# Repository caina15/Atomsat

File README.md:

# Atomsat
Atomsat is a 9-member project, the aim of the project is to develop and launch a low-cost cubesat 1U (nano satellite in cube format 10 by 10 by 10 cm) for technology demonstration and open doors for scientific experiments in schools around the world . The launch estimate is for the beginning of 2024 and is expected to be in operation for 1 year (caused by orbital decay).
(The project is still under development, codes and PCBs are not ready)

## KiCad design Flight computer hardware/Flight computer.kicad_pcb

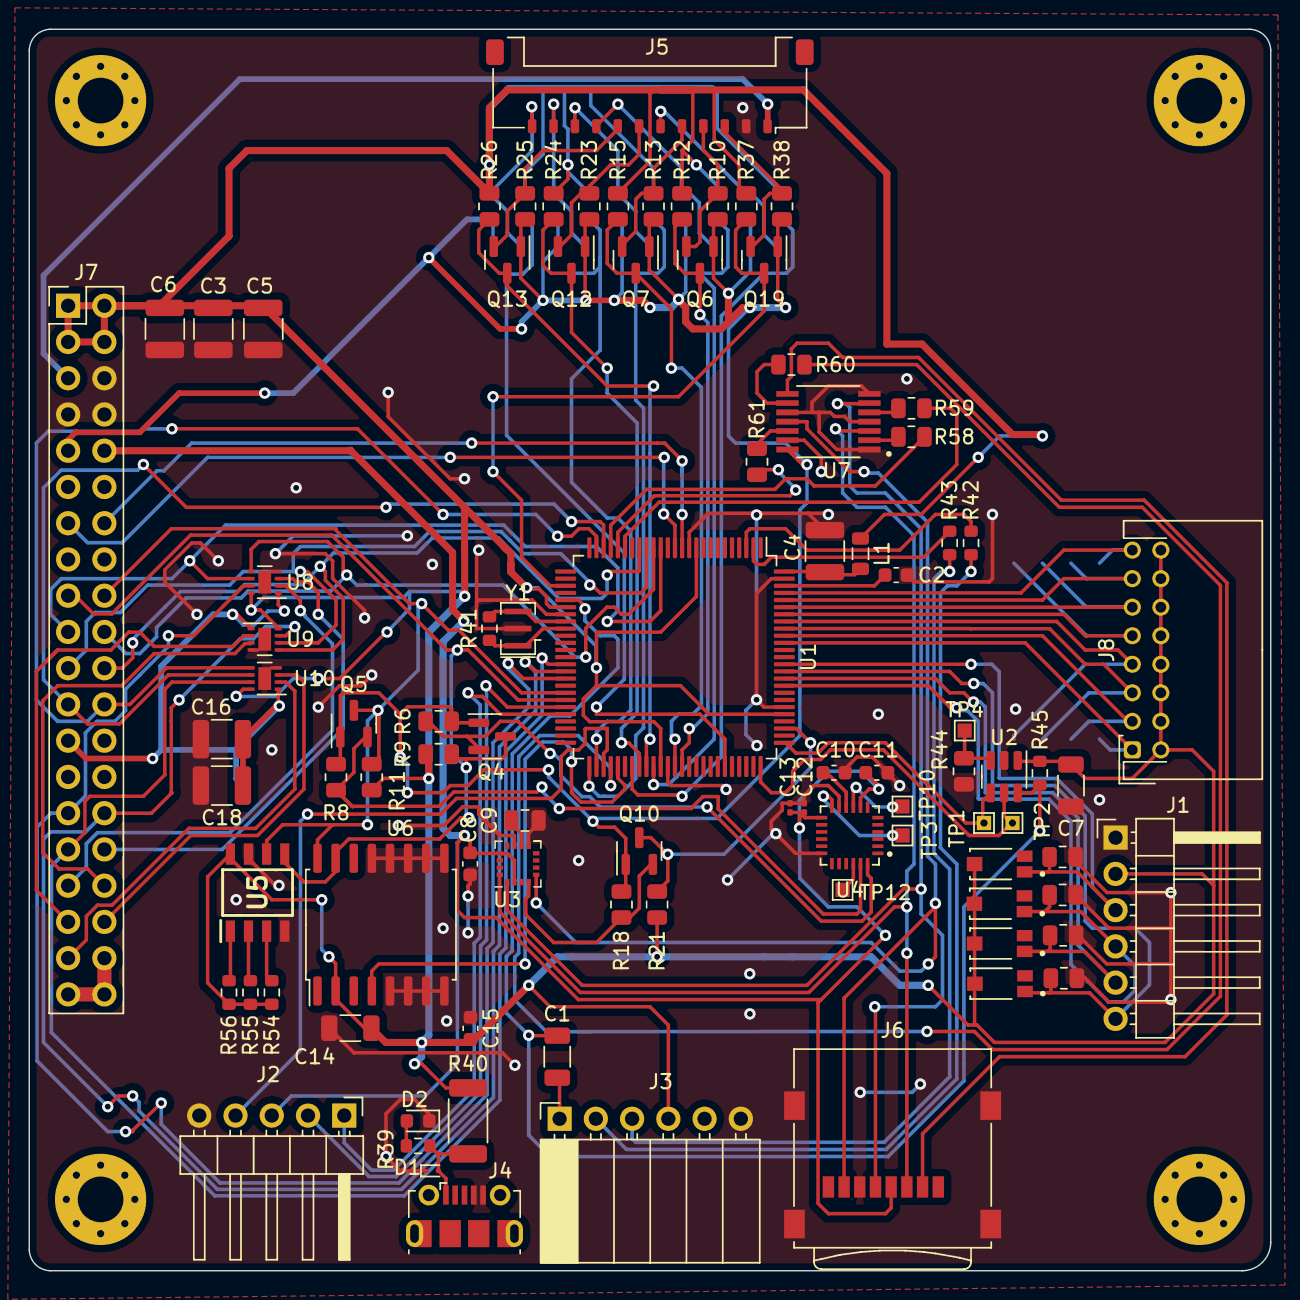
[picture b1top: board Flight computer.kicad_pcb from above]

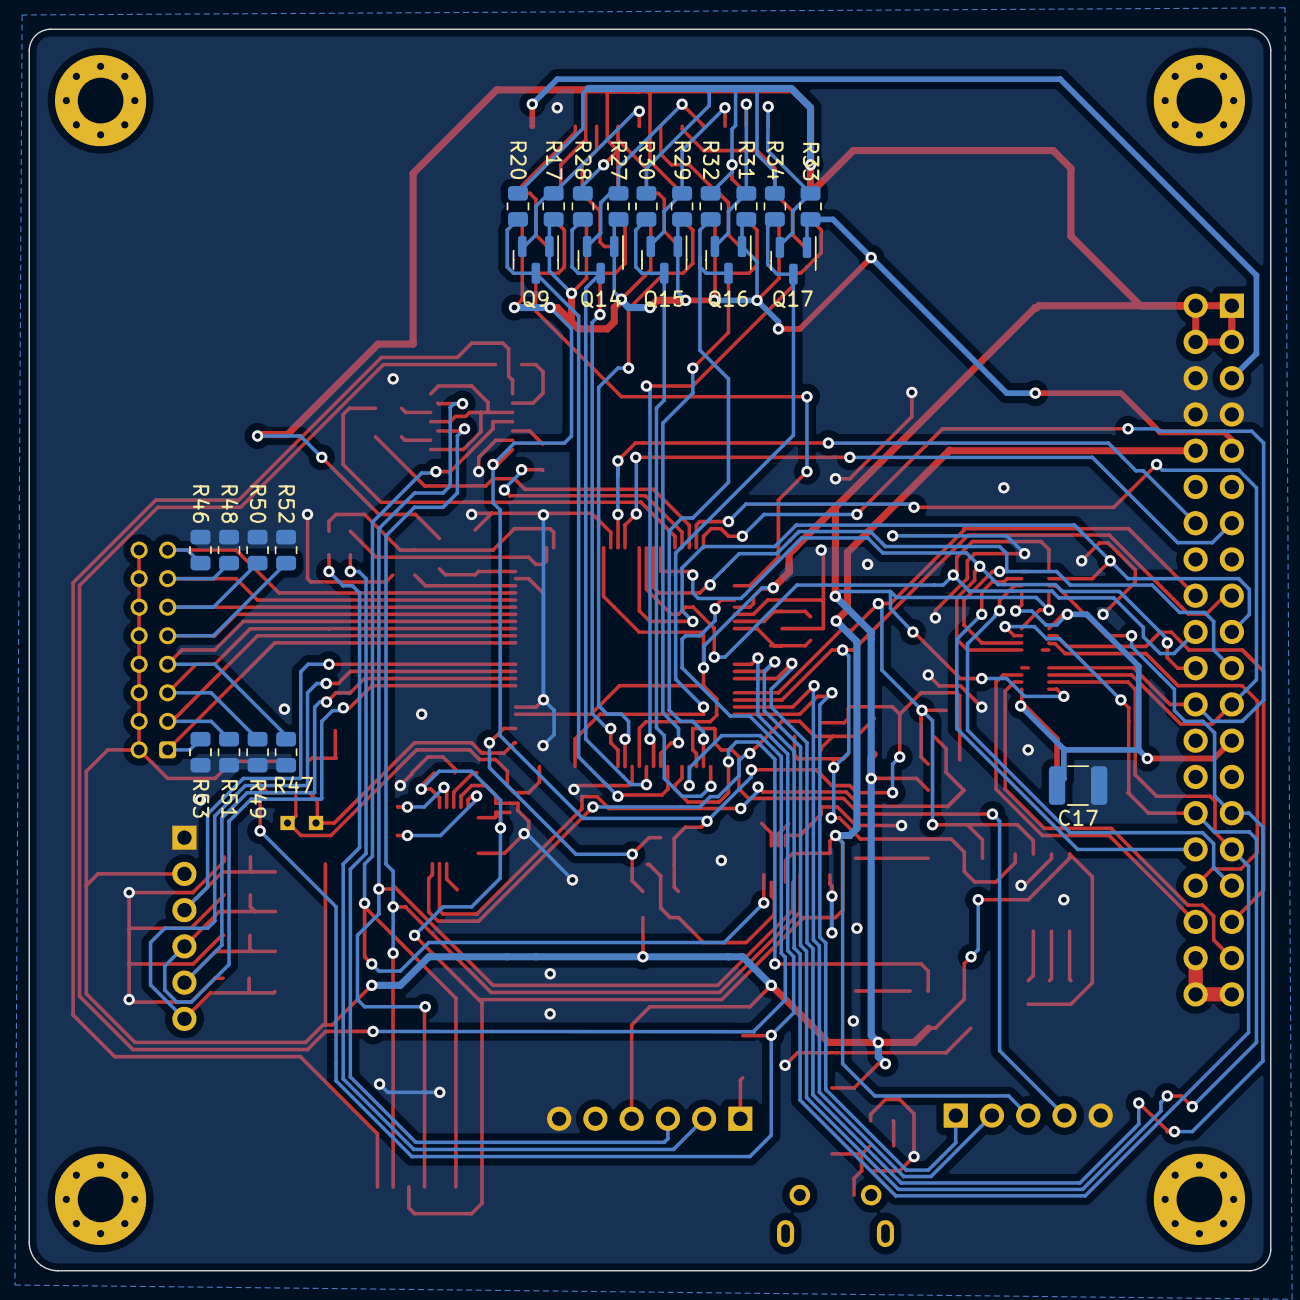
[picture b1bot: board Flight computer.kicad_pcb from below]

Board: 2 copper layers, 87.0 x 87.0 mm, 119 parts (24 on the bottom side), 101 nets.

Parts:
C1, C7, C14: 0.1uF; C_1206_3216Metric
C2: 100nF; C_0603_1608Metric
C3, C4, C5, C6, C16, C17, C18: 100nF; C_1210_3225Metric
C8, C15: 1uF; C_0603_1608Metric
C9: 10uF; C_0805_2012Metric
C10: 0.47uF; C_0603_1608Metric
C11: 10nF; C_0603_1608Metric
C12, C13: 2.2uF; C_0201_0603Metric
D1: ESD9B5.0ST5G; D_SOD-923
D2: LED_smd; LED_0603_1608Metric
H1, H2, H3, H4: MountingHole; MountingHole_3.2mm_M3_Pad_Via
J1: Conn_01x06_Male; PinHeader_1x06_P2.54mm_Horizontal
J2: Conn_01x05_Male; PinHeader_1x05_P2.54mm_Horizontal
J3: Conn_01x06_Female; PinSocket_1x06_P2.54mm_Horizontal
J4: USB_B; USB_Micro-B_Molex-105017-0001
J5: Conn_01x12_Male; Molex_Pico-Lock_504050-1291_1x12-1MP_P1.50mm_Horizontal
J6: Micro_SD_Card; microSD_HC_Wuerth_693072010801
J7: Conn_02x20_Odd_Even; PinHeader_2x20_P2.54mm_Vertical
J8: Conn_01x16_Male; JST_PHD_S16B-PHDSS_2x08_P2.00mm_Horizontal
L1: 10uH; L_0805_2012Metric
Q1, Q2, Q3, Q8: TEMT6000X01; TRANS_TEMT6000X01
Q4, Q5, Q6, Q7, Q9, Q10, Q12, Q13, Q14, Q15, Q16, Q17, Q19: BSS138; SOT-23
R1, R2, R3, R4, R6, R8, R18, R38, R46, R47, R48, R49, R50, R51, R52, R53: 10K; R_0805_2012Metric
R9, R11, R21, R37: 10k; R_0805_2012Metric
R10, R12, R13, R15, R17, R20, R23, R24, R25, R26, R27, R28, R29, R30, R31, R32, R33, R34: 100K; R_0805_2012Metric
R39: 330; R_0603_1608Metric
R40: 10m; R_2010_5025Metric
R41: 1M; R_0603_1608Metric
R42, R43: 1K; R_0603_1608Metric
R44: 8.87K; R_0805_2012Metric
R45: 10K; R_0603_1608Metric
R54, R55, R56: 4.7K; R_0603_1608Metric
R58, R59, R60, R61: 3.3K; R_0805_2012Metric
TP1, TP2: TP_1x1; TestPoint_THTPad_1.0x1.0mm_Drill0.5mm
TP3, TP4, TP10, TP12: TP_smt_1x1; TestPoint_Pad_1.0x1.0mm
U1: ATmega2560-16A; TQFP-100_14x14mm_P0.5mm
U2: TPL5010; SOT-23-6
U3: MMC5983MA; LGA-16_3x3mm_P0.5mm
U4: ICM-20689; QFN50P400X400X95-24N
U5: AT24C32D-SSHM-B; SOIC127P600X175-8N
U6: DS3231M; SOIC-16W_7.5x10.3mm_P1.27mm
U7: SN74LVC125APWT; SOP65P640X120-14N
U8, U9, U10: DRV8837; WSON-8-1EP_2x2mm_P0.5mm_EP0.9x1.6mm
Y1: 16Mhz; Resonator_SMD_Murata_CSTxExxV-3Pin_3.0x1.1mm

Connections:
3.3V_LOGIC: J7.9, Q4.1 (G), Q5.1 (G), Q6.1 (G), Q7.1 (G), Q9.1 (G), Q10.1 (G), Q12.1 (G), Q13.1 (G), Q14.1 (G), Q15.1 (G), Q16.1 (G), Q17.1 (G), Q19.1 (G), R6.1, R8.1, R10.1, R13.1, R17.1, R18.1, R23.1, R25.1, R27.1, R29.1, R31.1, R33.1, R38.1, U7.14 (VCC)
5V_COIL: C16.2, C17.2, C18.2, J7.25, U8.1 (VM), U9.1 (VM), U10.1 (VM)
+3.3V: C8.1, C11.1, C12.1, C13.1, J2.3, J6.4 (VDD), J7.10, U3.2 (VDD), U3.13 (VDDIO), U4.8 (VDDIO), U4.13 (VDD)
+5V: C3.2, C5.2, C6.2, C7.2, C14.2, C15.2, J1.2, J3.4, J7.1, J7.2, J7.3, J7.4, J8.2, J8.4, J8.6, J8.8, J8.10, J8.12, J8.14, J8.16, L1.2, Q1.3, Q2.3, Q3.3, Q8.3, R9.1, R11.1, R12.1, R15.1, R20.1, R21.1, R24.1, R26.1, R28.1, R30.1, R32.1, R34.1, R37.1, R40.2, R45.2, R54.1, R55.1, R56.1, U1.10 (VCC), U1.31 (VCC), U1.61 (VCC), U1.80 (VCC), U2.1 (VDD), U5.8 (VCC), U6.2 (VCC), U8.8 (VCC), U9.8 (VCC), U10.8 (VCC)
/2560/ADC1: J8.13, R48.2, U1.96 (PF1)
/2560/ADC2: J8.11, R50.2, U1.95 (PF2)
/2560/ADC3: J8.9, R52.2, U1.94 (PF3)
/2560/ADC4: J8.7, R47.2, U1.93 (PF4)
/2560/ADC5: J8.5, R49.2, U1.92 (PF5)
/2560/ADC6: J8.3, R51.2, U1.91 (PF6)
/2560/ADC7: J8.1, R53.2, U1.90 (PF7)
/2560/ADCO: J8.15, R46.2, U1.97 (PF0)
/2560/AREF: C2.2, U1.98 (AREF)
/2560/PA0: Q10.3 (D), R21.2, U1.78 (PA0)
/2560/RX2: J7.14, U1.12 (PH0)
/2560/TX2: J7.13, U1.13 (PH1)
/GYRO/INT: TP3.1, U4.12 (INT)
/GYRO/NCS: TP12.1, U4.22 (NCS)
/GYRO/SCL: Q5.2 (S), R8.2, U4.23 (SCL/SCLK)
/GYRO/SDA: Q4.2 (S), R6.2, U4.24 (SDA/SDI)
/GYRO/SDO: TP10.1, U4.9 (AD0/SDO)
/MAG/CS: Q10.2 (S), R18.2, U3.4 (SPI_CS)
/conn/P_solar: J7.38, J7.39, J7.40
ACS_X_SP: J7.29, U1.41 (PL6), U8.7 (~SLEEP)
ACS_Y_SP: J7.30, U1.40 (PL5), U9.7 (~SLEEP)
ACS_Z_SP: J7.31, U1.39 (PL4), U10.7 (~SLEEP)
CS_SD: R60.2, U1.54 (PC1)
CS_SD_3.3: J6.2 (DAT3/CD), U7.8 (3Y)
DF_CTS: J5.8, Q13.2 (S), R25.2
DF_DCD: J5.6, Q9.2 (S), R17.2
DF_DSR: J5.7, Q12.2 (S), R23.2
DF_DTR: J5.11, Q16.2 (S), R31.2
DF_RI: J5.9, Q14.2 (S), R27.2
DF_RTS: J5.10, Q15.2 (S), R29.2
DF_S_RX: J5.5, Q7.2 (S), R13.2
DF_S_TX: J5.4, Q6.2 (S), R10.2
DONE: TP1.1, U1.76 (PA2), U2.4 (DONE)
EN_X: J7.20, U1.16 (PH4), U8.5 (IN2)
EN_Y: J7.22, U1.18 (PH6), U9.5 (IN2)
EN_Z: J7.24, U1.24 (PB5), U10.5 (IN2)
EXT_PWR: J5.1, J7.5
FC_RX3: Q7.3 (D), R15.2, U1.63 (PJ0)
FC_TX3: Q6.3 (D), R12.2, U1.64 (PJ1)
GND: C2.1, C3.1, C4.1, C5.1, C6.1, C7.1, C8.2, C9.2, C10.2, C11.2, C12.2, C13.2, C14.1, C15.1, C16.1, C17.1, C18.1, D1.1 (A1), D2.1 (K), J1.1, J2.5, J3.6, J4.4 (GND), J4.5 (Shield), J5.2, J6.6 (VSS), J6.9 (SHIELD), J7.6, J7.7, J7.8, R1.2, R2.2, R3.2, R4.2, R44.2, R46.1, R47.1, R48.1, R49.1, R50.1, R51.1, R52.1, R53.1, U1.11 (GND), U1.32 (GND), U1.62 (GND), U1.81 (GND), U1.99 (GND), U2.2 (GND), U3.9 (VSS), U3.11 (VSS), U4.11 (FSYNC), U4.18 (GND), U5.4 (GND), U5.7 (WP), U6.5 (GND), U6.6 (GND), U6.7 (GND), U6.8 (GND), U6.9 (GND), U6.10 (GND), U6.11 (GND), U6.12 (GND), U6.13 (GND), U7.1 (1~OE), U7.4 (2~OE), U7.7 (GND), U7.10 (3~OE), U7.13 (4~OE), U8.4 (GND), U8.9 (GND), U9.4 (GND), U9.9 (GND), U10.4 (GND), U10.9 (GND), Y1.2
MISO_3.3V: J6.7 (DAT0), U3.5 (SPI_SDO), U7.11 (4Y)
MISO_5V: R61.2, U1.21 (PB2)
MOSI_3.3V: J6.3 (CMD), U3.16 (SDA/SPI_SDI), U7.3 (1Y)
MOSI_5V: R58.2, U1.22 (PB3)
NET_AVAILABLE: J5.12, Q17.2 (S), R33.2
unnamed: C1.2, J3.1
unnamed: C4.2, L1.1, U1.100 (AVCC)
unnamed: C9.1, U3.10 (CAP)
unnamed: C10.1, U4.10 (REGOUT)
unnamed: D1.2 (A2), J4.1 (VBUS), R39.2, R40.1
unnamed: D2.2 (A), R39.1
unnamed: J5.3, Q19.2 (S), R38.2
unnamed: R41.1, U1.34 (XTAL1), Y1.1
unnamed: R41.2, U1.33 (XTAL2), Y1.3
unnamed: R42.1, U1.3 (PE1)
unnamed: R43.1, U1.2 (PE0)
unnamed: R44.1, TP4.1, U2.3 (DELAY/M_RST)
unnamed: R54.2, U5.3 (A2)
unnamed: R55.2, U5.2 (A1)
unnamed: R56.2, U5.1 (A0)
unnamed: R58.1, U7.2 (1A)
unnamed: R59.1, U7.5 (2A)
unnamed: R60.1, U7.9 (3A)
unnamed: R61.1, U7.12 (4A)
ON/OFF_iridium: Q19.3 (D), R37.2, U1.28 (PG3)
OUT1X: J7.33, U8.2 (OUT1)
OUT1Y: J7.35, U9.2 (OUT1)
OUT1Z: J7.37, U10.2 (OUT1)
OUT2X: J7.32, U8.3 (OUT2)
OUT2Y: J7.34, U9.3 (OUT2)
OUT2Z: J7.36, U10.3 (OUT2)
PC4: Q9.3 (D), R20.2, U1.57 (PC4)
PC5: Q12.3 (D), R24.2, U1.58 (PC5)
PC6: Q13.3 (D), R26.2, U1.59 (PC6)
PC7: Q14.3 (D), R28.2, U1.60 (PC7)
PG0: Q15.3 (D), R30.2, U1.51 (PG0)
PG1: Q16.3 (D), R32.2, U1.52 (PG1)
PG2: Q17.3 (D), R34.2, U1.70 (PG2)
PH_X: J7.19, U1.15 (PH3), U8.6 (IN1)
PH_Y: J7.21, U1.17 (PH5), U9.6 (IN1)
PH_Z: J7.23, U1.23 (PB4), U10.6 (IN1)
RESET: C1.1, R45.1, U1.30 (~RESET), U2.6 (~RST)
RESET_GPS: J2.4, U1.53 (PC0)
RX0: J3.3, R43.2
RX_GPS: J2.2, U1.45 (PD2)
S1: J1.3, Q1.1, R1.1, U1.87 (PK2)
S2: J1.6, Q8.1, R4.1, U1.86 (PK3)
S3: J1.5, Q3.1, R3.1, U1.85 (PK4)
S4: J1.4, Q2.1, R2.1, U1.84 (PK5)
SCK_3.3V: J6.5 (CLK), U3.1 (SCL/SPI_SCK), U7.6 (2Y)
SCK_5V: R59.2, U1.20 (PB1)
SCL: J7.18, Q5.3 (D), R11.2, U1.43 (PD0), U5.6 (SCL), U6.16 (SCL)
SDA: J7.17, Q4.3 (D), R9.2, U1.44 (PD1), U5.5 (SDA), U6.15 (SDA)
TX0: J3.2, R42.2
TX_GPS: J2.1, U1.46 (PD3)
WAKE: TP2.1, U1.75 (PA3), U2.5 (WAKE)
rst_ds: U1.55 (PC2), U6.4 (~RST)

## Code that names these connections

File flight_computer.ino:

#include "RTClib.h"
#include "Wire.h"
#include <SPI.h>
#include "ICM20689.h"
#include <SparkFun_MMC5983MA_Arduino_Library.h> //Click here to get the library: http://librarymanager/All#SparkFun_MMC5983MA
#include <SD.h>

void mag();
void gyro();

File dataFile;
SFE_MMC5983MA myMag;

#define csmag  PA0 //mega pin 22
#define rst_ds PC2 //mega pin 35

#define PH_X  PH3 //mega pin 6
#define EN_X  PH4 //mega pin 7
#define SP_X  PL4 //mega pin 45
#define PH_Y  PH5 //mega pin 8
#define EN_Y  PH6 //mega pin 9
#define SP_Y  PL5 //mega pin 44
#define PH_Z  PB4 //mega pin 10
#define EN_Z  PB5 //mega pin 11
#define SP_Z  PL6 //mega pin 43

ICM20689 IMU(Wire,0x68);

RTC_DS3231 rtc;

int statusINM;
uint32_t currentX, currentY, currentZ = 0;  //MAG
double normalizedX, normalizedY, normalizedZ = 0; //MAG
unsigned long millisgeralpre = 0; //SD
const long intervaloSD = 500; //SD
int celsius = 0;  //MAG
int PHX, ENX, SPX = 0; //ACS X
int PHY, ENY, SPY = 0; //ACS Y
int PHZ, ENZ, SPZ = 0; //ACS Z
String receEarth, codRTC;
DateTime ajsttime;

void setup()
{
 PORTC = PORTC | (1<< PC2);
 
  Serial.begin(115200);
  Serial1.begin(9600);
  Serial2.begin(115200);
  
  while(!Serial) {}
  SPI.begin();
  
  Serial.print("Initializing SD card...");
  if (!SD.begin(4)) {
    Serial.println("initialization failed!");
  }else{
    Serial.println("initialization done.");
  }

  // start communication with IMU
  statusINM = IMU.begin();
  if (statusINM < 0) {
    Serial.println("IMU initialization unsuccessful");
    Serial.print("statusINM: ");
    Serial.println(statusINM);
  }
  Serial.println("temp ICM20689,X Mag axis raw value,Y Mag axis raw value,Z Mag axis raw value,X axis field (Gauss),Y axis field (Gauss),Z axis field (Gauss),ax,ay,az,gx,gy,gz,temp_C");

    if (myMag.begin(csmag) == false)
    {
      Serial.println("MMC5983MA did not respond");
    }else{
    Serial.println("MMC5983MA connected");
    }
    myMag.softReset();
}

void loop()
{
unsigned long millisgeral = millis();  
  mag();
  gyro();
  if (millisgeral - millisgeralpre >= intervaloSD) {
    millisgeralpre = millisgeral;
    dataFile = SD.open("data.txt", FILE_WRITE);
    if (dataFile){
      dataFile.print(celsius);
      dataFile.print("\t");
      dataFile.print(currentX);
      dataFile.print("\t");
      dataFile.print(currentY);
      dataFile.print("\t");
      dataFile.print(currentZ);
      dataFile.print("\t");
      dataFile.print(normalizedX * 8, 5); // Print with 5 decimal places
      dataFile.print("\t");    
      dataFile.print(normalizedY * 8, 5);
      dataFile.print("\t");
      dataFile.print(normalizedZ * 8, 5);
      dataFile.print("\t");
      dataFile.print(IMU.getAccelX_mss(),6);
      dataFile.print("\t");
      dataFile.print(IMU.getAccelY_mss(),6);
      dataFile.print("\t");
      dataFile.print(IMU.getAccelZ_mss(),6);
      dataFile.print("\t");
      dataFile.print(IMU.getGyroX_rads(),6);
      dataFile.print("\t");
      dataFile.print(IMU.getGyroY_rads(),6);
      dataFile.print("\t");
      dataFile.print(IMU.getGyroZ_rads(),6);
      dataFile.print("\t");
      dataFile.print(IMU.getTemperature_C(),6);   
      dataFile.println();

      dataFile.close();
      Serial.print(F("SD write"));
    }else {
    Serial.print(F("error write"));
    }
  }  
}
void mag(){
  
  int celsius = myMag.getTemperature();
  float fahrenheit = (celsius * 9.0f / 5.0f) + 32.0f;
  Serial.print(celsius);
  Serial.print("\t"); 
  
  // This reads the X, Y and Z channels mag consecutively
  currentX = myMag.getMeasurementX();
  currentY = myMag.getMeasurementY();
  currentZ = myMag.getMeasurementZ();

  // Or, we could read all three simultaneously
  //myMag.getMeasurementXYZ(&currentX, &currentY, &currentZ);

  Serial.print(currentX);
  Serial.print("\t");
  Serial.print(currentY);
  Serial.print("\t");
  Serial.print(currentZ);
  Serial.print("\t");

  // The magnetic field values are 18-bit unsigned. The zero (mid) point is 2^17 (131072).
  // Normalize each field to +/- 1.0
  normalizedX = (double)currentX - 131072.0;
  normalizedX /= 131072.0;
  normalizedY = (double)currentY - 131072.0;
  normalizedY /= 131072.0;
  normalizedZ = (double)currentZ - 131072.0;
  normalizedZ /= 131072.0;
  
  // The magnetometer full scale is +/- 8 Gauss
  // Multiply the normalized values by 8 to convert to Gauss
  Serial.print(normalizedX * 8, 5); // Print with 5 decimal places
  Serial.print("\t");    
  Serial.print(normalizedY * 8, 5);
  Serial.print("\t");
  Serial.print(normalizedZ * 8, 5);
  Serial.print("\t");
    
}
void gyro(){
  // read the sensor
  IMU.readSensor();
  // display the data
  Serial.print(IMU.getAccelX_mss(),6);
  Serial.print("\t");
  Serial.print(IMU.getAccelY_mss(),6);
  Serial.print("\t");
  Serial.print(IMU.getAccelZ_mss(),6);
  Serial.print("\t");
  Serial.print(IMU.getGyroX_rads(),6);
  Serial.print("\t");
  Serial.print(IMU.getGyroY_rads(),6);
  Serial.print("\t");
  Serial.print(IMU.getGyroZ_rads(),6);
  Serial.print("\t");
  Serial.print(IMU.getTemperature_C(),6);   
  Serial.println(); 
  }
void ACS(){
  //CONTROL ACS
  digitalWrite(SP_X, SPX);  //Set direction X
  digitalWrite(PH_X, PHX);  //enable X
  analogWrite(EN_X, ENX);   //control X
    
  digitalWrite(SP_X, SPX);  //Set direction Y
  digitalWrite(PH_X, PHX);  //enable Y
  analogWrite(EN_X, ENX);   //control Y
  
  digitalWrite(SP_X, SPX);  //Set direction Z
  digitalWrite(PH_X, PHX);  //enable Z
  analogWrite(EN_X, ENX);   //control Z
}
void RTCds(){
  
  DateTime now = rtc.now(); // get the current time
//para receber dados usar assim\/\/
/*
  Serial.print(now.year(), DEC);
  Serial.print('/');
  Serial.print(now.month(), DEC);
  Serial.print('/');
  Serial.print(now.day(), DEC);
  Serial.print(' ');
  Serial.print(now.hour(), DEC);
  Serial.print(':');
  Serial.print(now.minute(), DEC);
  Serial.print(':');
  Serial.print(now.second(), DEC);
  Serial.println();  
*/  
}
void RebDataRTC(){
  if(receEarth == codRTC){
    rtc.adjust(ajsttime); //(ANO), (MÊS), (DIA), (HORA), (MINUTOS), (SEGUNDOS)
  }
}

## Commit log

2023-02-12 Add files via upload
    code in C++ of flight computer
2023-02-12 Rename flcube.ino to flight_computer.ino
    Developing
2023-02-12 Developing (BETA)
2023-02-12 Create images
2023-02-12 images of cubesat
2023-02-12 Update README.md
    correct error
2023-02-12 Create flight_computer_Board
2023-02-12 Create about
2023-02-12 Add files via upload
    KiCad Board
2023-02-12 flight computer KiCad
2023-02-19 Create 1
2023-02-19 atualização ACS
2023-02-20 Declared void mag and void gyro
2023-02-20 add ajsttime to update the time
2023-02-26 new version
